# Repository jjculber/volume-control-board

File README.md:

# volume-control-board

Volume? Level?

The goal of this project is to make a small PCB for controlling volume with a rotary encoder and digital potentiometer.

- __Audio Input__: 3.5mm TRS jack
- __Digital Potentiometer__: AD5254 (4 circuits, 256 taps, 10k or 50k ohms)
- __Audio Output__: Shielded RJ45 for sending 4 channels to amplifier with cat6

[schematic](hardware/schematic.pdf)

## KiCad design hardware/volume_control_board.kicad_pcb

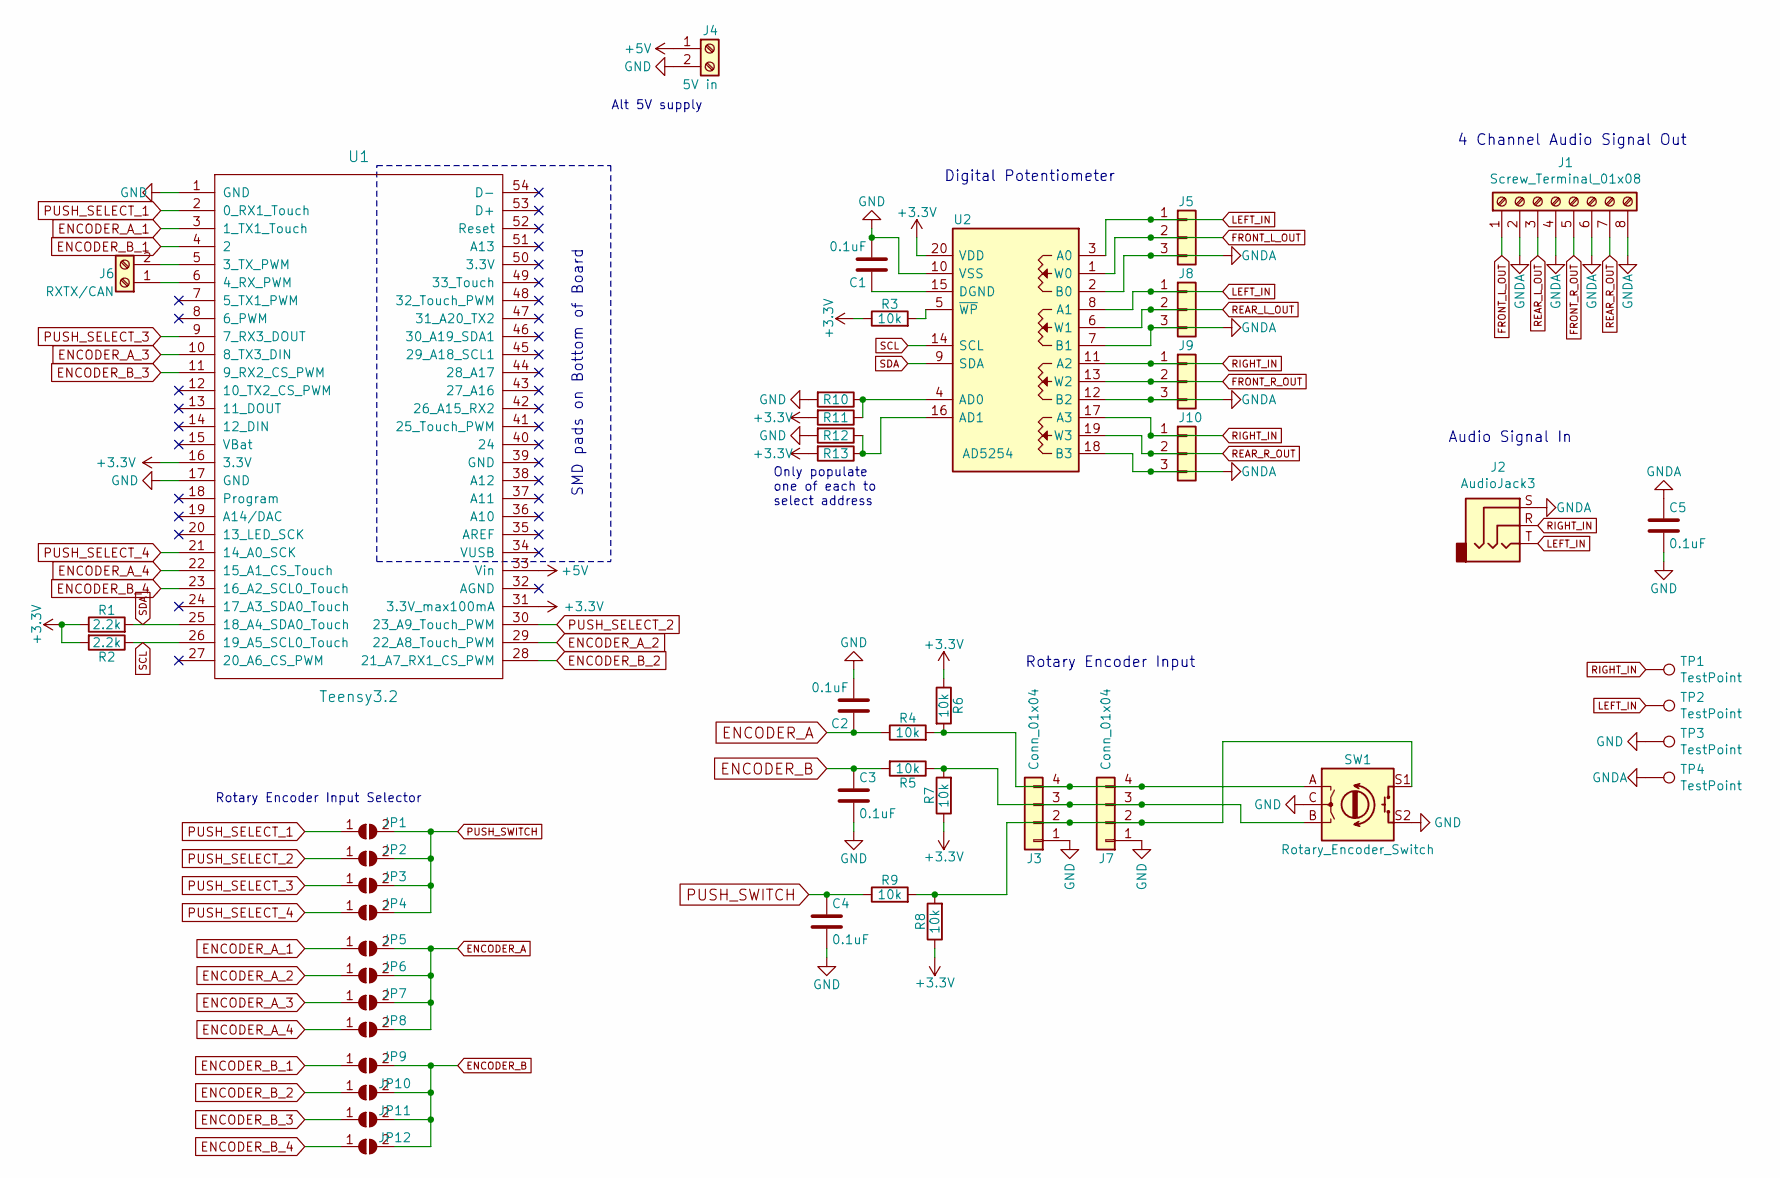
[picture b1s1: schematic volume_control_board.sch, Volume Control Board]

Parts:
C1, C2, C3, C4, C5: 0.1uF; C_0805
J1: Screw_Terminal_01x08; Socket_Strip_Straight_1x08_Pitch2.54mm
J2: AudioJack3; Jack_3.5mm_CUI_SJ-3523-SMT_Horizontal
J3, J7: Conn_01x04; Grove_1x04
J4: 5V in; Socket_Strip_Straight_1x02_Pitch2.54mm
J5, J8, J9, J10: Conn_01x03; Socket_Strip_Straight_1x03_Pitch2.00mm
J6: RXTX/CAN; Socket_Strip_Straight_1x02_Pitch2.54mm
JP1, JP2, JP3, JP4, JP5, JP6, JP7, JP8, JP9, JP10, JP11, JP12: SolderJumper_2_Open; SolderJumper-2_P1.3mm_Open_RoundedPad1.0x1.5mm
R1, R2: 2.2k; R_0805
R3, R4, R5, R6, R7, R8, R9: 10k; R_0805
R10, R11, R12, R13: R; R_0805
SW1: Rotary_Encoder_Switch; RotaryEncoder_Alps_EC11E-Switch_Vertical_H20mm
TP1, TP2, TP3, TP4: TestPoint; Measurement_Point_Round-TH_Small
U1: Teensy3.2; Teensy30_31_32_LC
U2: AD5254; TSSOP-20_4.4x6.5mm_Pitch0.65mm

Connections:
+3V3: R1.1, R2.2, R3.1, R6.1, R7.1, R8.1, R11.2, R13.2, U1.16 (3.3V), U1.31 (3.3V_max100mA), U2.20 (VDD)
+5V: J4.1, U1.33 (Vin)
ENCODER_A: C2.1, JP5.2 (B), JP6.2 (B), JP7.2 (B), JP8.2 (B), R4.1
ENCODER_A_1: JP5.1 (A), U1.3 (1_TX1_Touch)
ENCODER_A_2: JP6.1 (A), U1.29 (22_A8_Touch_PWM)
ENCODER_A_3: JP7.1 (A), U1.10 (8_TX3_DIN)
ENCODER_A_4: JP8.1 (A), U1.22 (15_A1_CS_Touch)
ENCODER_B: C3.1, JP9.2 (B), JP10.2 (B), JP11.2 (B), JP12.2 (B), R5.2
ENCODER_B_1: JP9.1 (A), U1.4 (2)
ENCODER_B_2: JP10.1 (A), U1.28 (21_A7_RX1_CS_PWM)
ENCODER_B_3: JP11.1 (A), U1.11 (9_RX2_CS_PWM)
ENCODER_B_4: JP12.1 (A), U1.23 (16_A2_SCL0_Touch)
FRONT_L_OUT: J1.1, J5.2, U2.1 (W0)
FRONT_R_OUT: J1.5, J9.2, U2.13 (W2)
GND: C1.2, C2.2, C3.2, C4.2, C5.2, J3.1, J4.2, J7.1, R10.2, R12.2, SW1.C, SW1.S2, TP3.1, U1.1 (GND), U1.17 (GND), U2.10 (VSS)
GNDA: C5.1, J1.2, J1.4, J1.6, J1.8, J2.S, J5.3, J8.3, J9.3, J10.3, TP4.1, U2.2 (B0), U2.7 (B1), U2.12 (B2), U2.18 (B3)
LEFT_IN: J2.T, J5.1, J8.1, TP2.1, U2.3 (A0), U2.8 (A1)
unnamed: C1.1, U2.15 (DGND)
unnamed: J3.2, J7.2, R8.2, R9.2, SW1.S1
unnamed: J3.3, J7.3, R5.1, R7.2, SW1.B
unnamed: J3.4, J7.4, R4.2, R6.2, SW1.A
unnamed: J6.1, U1.6 (4_RX_PWM)
unnamed: J6.2, U1.5 (3_TX_PWM)
unnamed: R3.2, U2.5 (~WP~)
unnamed: R10.1, R11.1, U2.4 (AD0)
unnamed: R12.1, R13.1, U2.16 (AD1)
PUSH_SELECT_1: JP1.1 (A), U1.2 (0_RX1_Touch)
PUSH_SELECT_2: JP2.1 (A), U1.30 (23_A9_Touch_PWM)
PUSH_SELECT_3: JP3.1 (A), U1.9 (7_RX3_DOUT)
PUSH_SELECT_4: JP4.1 (A), U1.21 (14_A0_SCK)
PUSH_SWITCH: C4.1, JP1.2 (B), JP2.2 (B), JP3.2 (B), JP4.2 (B), R9.1
REAR_L_OUT: J1.3, J8.2, U2.6 (W1)
REAR_R_OUT: J1.7, J10.2, U2.19 (W3)
RIGHT_IN: J2.R, J9.1, J10.1, TP1.1, U2.11 (A2), U2.17 (A3)
SCL: R2.1, U1.26 (19_A5_SCL0_Touch), U2.14 (SCL)
SDA: R1.2, U1.25 (18_A4_SDA0_Touch), U2.9 (SDA)

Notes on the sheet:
4 Channel Audio Signal Out
Digital Potentiometer
Audio Signal In
Rotary Encoder Input
SMD pads on Bottom of Board
Rotary Encoder Input Selector
Only populate one of each to select address
Alt 5V supply

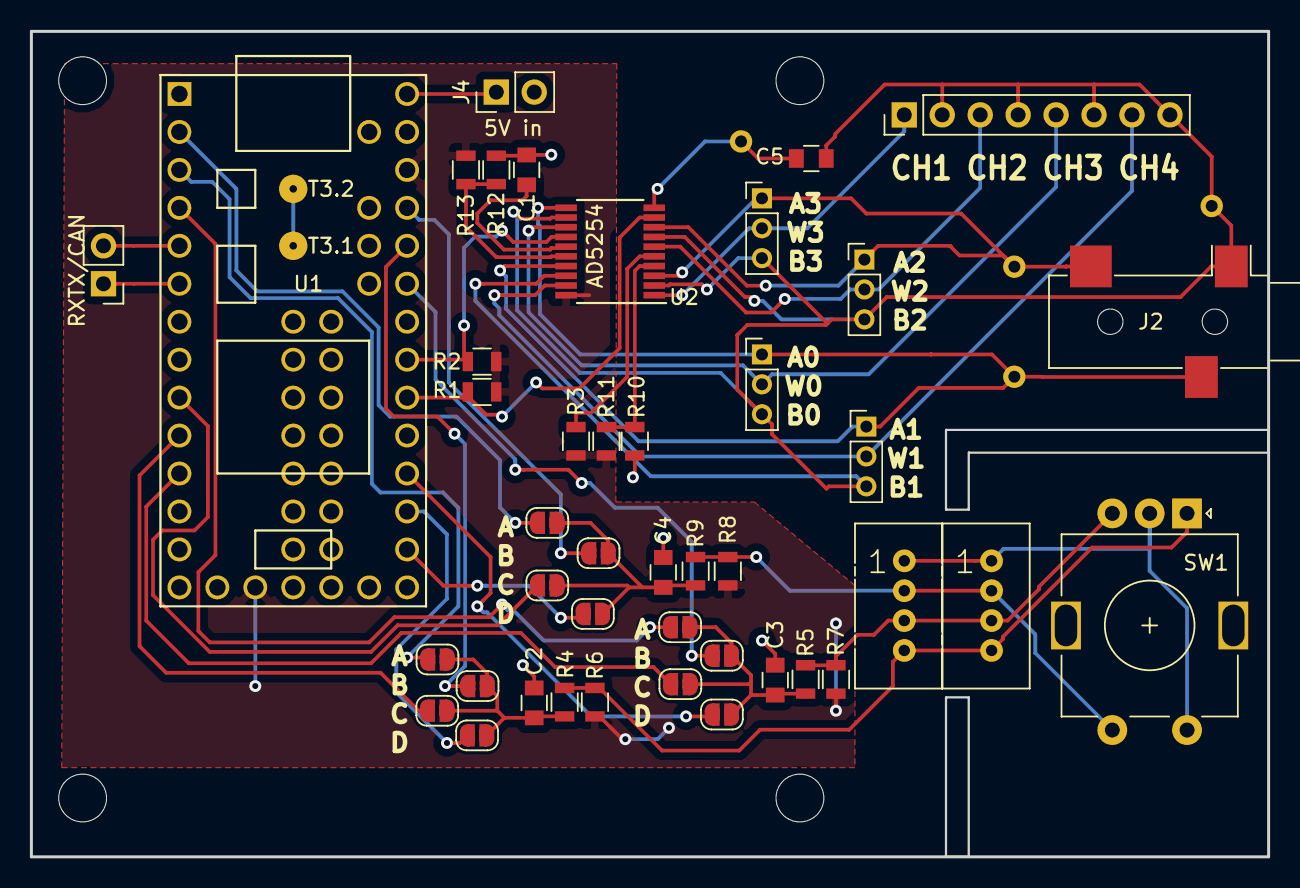
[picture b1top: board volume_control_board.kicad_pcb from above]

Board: 2 copper layers, 82.8 x 55.2 mm, 47 parts (0 on the bottom side), 36 nets.

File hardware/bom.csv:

Id,Designator,Package,Quantity,Designation,Supplier and ref,Note
1,J2,Jack_3.5mm_CUI_SJ-3523-SMT_Horizontal,1,AudioJack3,CP-3523SJCT-ND,
2,"REF**,REF**,REF**,REF**",MountingHole_2.2mm_M2,4,MountingHole_2.2mm_M2,,
3,"C1,C2,C3,C4,C5",C_0805,5,0.1uF,,
4,J1,Socket_Strip_Straight_1x08_Pitch2.54mm,1,Screw_Terminal_01x08,A98333-ND (x4),
5,"J4,J5",Socket_Strip_Straight_1x04_Pitch2.54mm,2,Conn_01x04,A98333-ND (x2),
6,J6,Socket_Strip_Straight_1x02_Pitch2.54mm,1,RXTX/CAN,A98333-ND,
7,"JP1,JP2,JP3,JP4,JP5,JP6,JP7,JP8,JP9,JP10,JP11,JP12",SolderJumper-2_P1.3mm_Open_RoundedPad1.0x1.5mm,12,SolderJumper_2_Open,,
8,"R1,R2",R_0805,2,2.2k,,
9,"R3,R4,R5,R6,R7,R8,R9",R_0805,7,10k,,
10,"R10,R11,R12,R13",R_0805,4,R,,
11,SW1,RotaryEncoder_Alps_EC11E-Switch_Vertical_H20mm,1,Rotary_Encoder_Switch,987-1188-ND,
12,U1,Teensy30_31_32_LC,1,Teensy3.2,1568-1231-ND,
13,U2,TSSOP-20_4.4x6.5mm_Pitch0.65mm,1,AD5254,AD5254BRUZ10-RL7CT-ND,
14,"J7,J3",Grove_1x04,2,Conn_01x04,455-1706-ND,6 inch jumper cable: 455-3151-ND

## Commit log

2019-02-02 Initial schematic layout.
2019-03-27 Added CS for Rotary Encoder and cleaned up a bit.
2019-03-27 finished first draft.
2019-04-05 firmware v1 and board v2
2019-04-06 added a few resistors for adjusting later.
2019-04-20 updated board with more breakouts.
2019-04-20 added silk pin descriptions.
